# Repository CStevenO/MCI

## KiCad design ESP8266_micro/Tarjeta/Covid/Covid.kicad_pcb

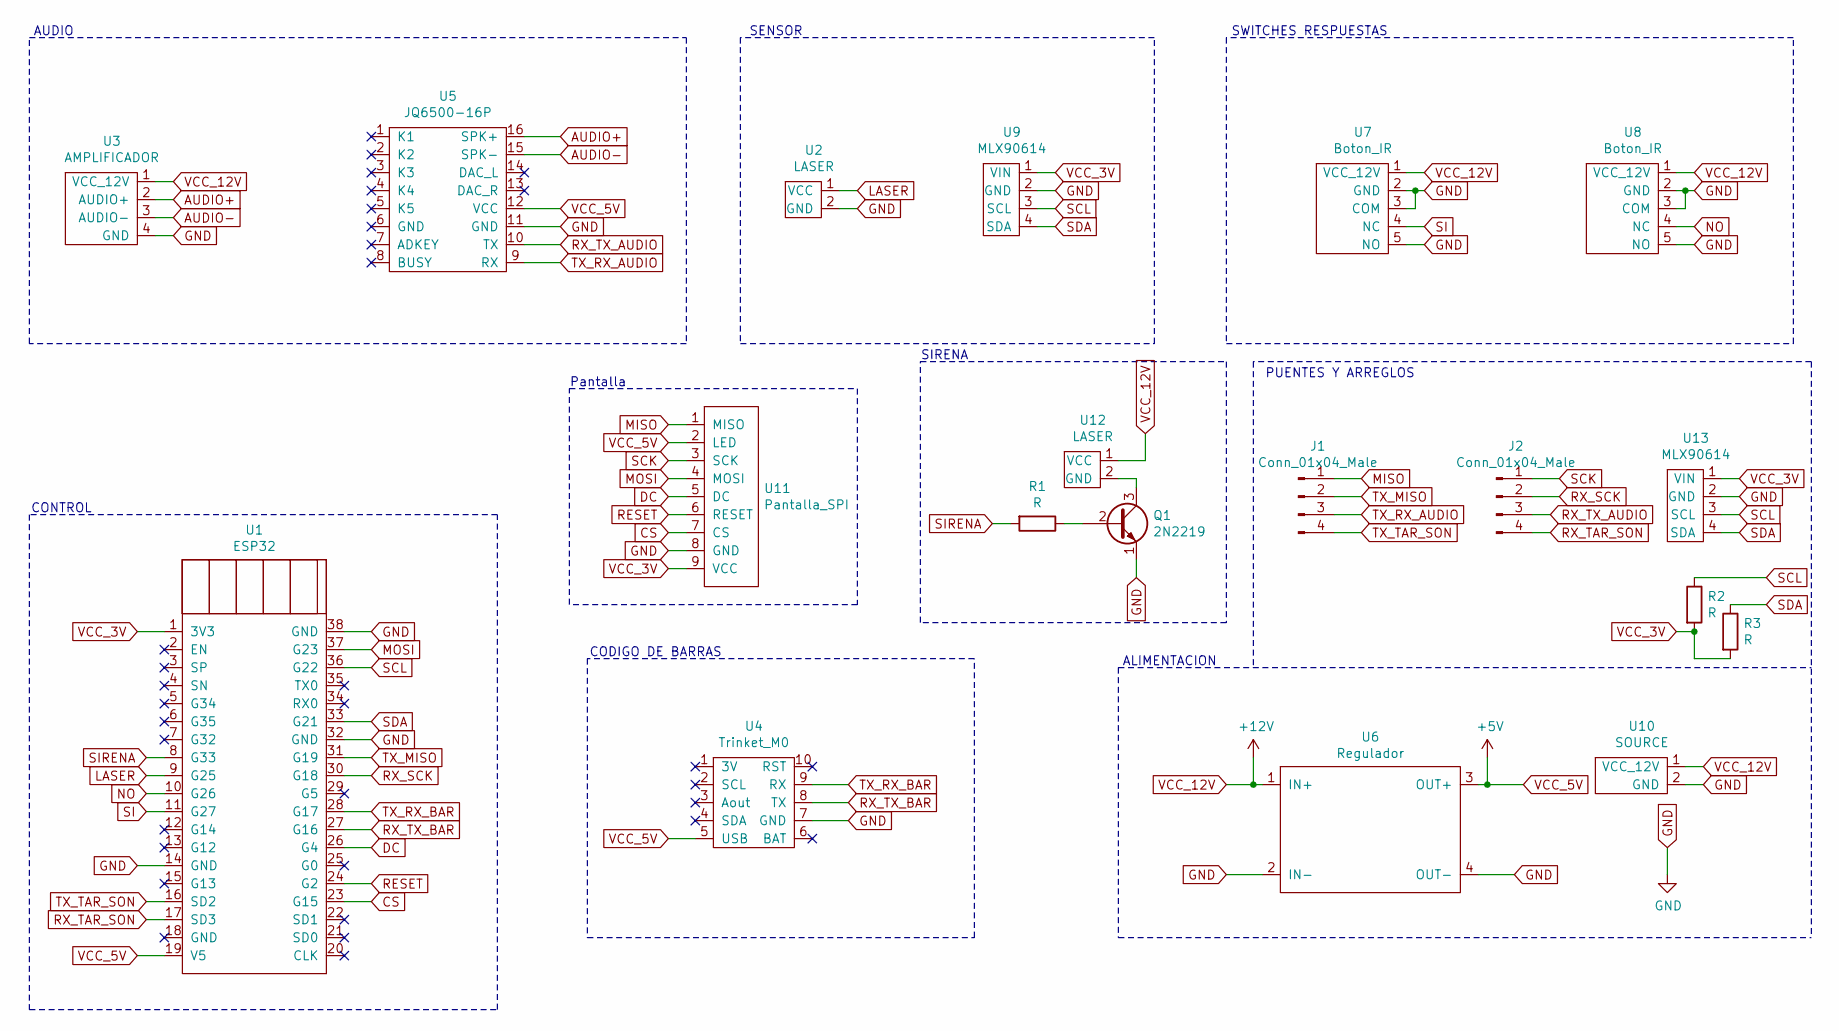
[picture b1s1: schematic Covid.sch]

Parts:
J1, J2: Conn_01x04_Male; TerminalBlock_TE_282834-4_1x04_P2.54mm_Horizontal
Q1: 2N2219; TO-92L_Inline
R1, R2, R3: R; R_Axial_DIN0309_L9.0mm_D3.2mm_P2.54mm_Vertical
U1: ESP32
U2, U12: LASER
U3: AMPLIFICADOR
U4: Trinket_M0; TRINKET_M0
U5: JQ6500-16P; JQ6500-16p
U6: Regulador
U7, U8: Boton_IR; BOTON_IR
U9: MLX90614; MXL90614
U10: SOURCE
U11: Pantalla_SPI; Pantalla_spi
U13: MLX90614; TerminalBlock_TE_282834-4_1x04_P2.54mm_Horizontal

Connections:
AUDIO+: U3.2 (AUDIO+), U5.16 (SPK+)
AUDIO-: U3.3 (AUDIO-), U5.15 (SPK-)
CS: U1.23 (G15), U11.7 (CS)
DC: U1.26 (G4), U11.5 (DC)
GND: Q1.1 (E), U1.14 (GND), U1.32 (GND), U1.38 (GND), U2.2 (GND), U3.4 (GND), U4.7 (GND), U5.11 (GND), U6.2 (IN-), U6.4 (OUT-), U7.2 (GND), U7.3 (COM), U7.5 (NO), U8.2 (GND), U8.3 (COM), U8.5 (NO), U9.2 (GND), U10.2 (GND), U11.8 (GND), U13.2 (GND)
LASER: U1.9 (G25), U2.1 (VCC)
MISO: J1.1, U11.1 (MISO)
MOSI: U1.37 (G23), U11.4 (MOSI)
NO: U1.10 (G26), U8.4 (NC)
unnamed: Q1.2 (B), R1.1
unnamed: Q1.3 (C), U12.2 (GND)
RESET: U1.24 (G2), U11.6 (RESET)
RX_SCK: J2.2, U1.30 (G18)
RX_TAR_SON: J2.4, U1.17 (SD3)
RX_TX_AUDIO: J2.3, U5.10 (TX)
RX_TX_BAR: U1.27 (G16), U4.8 (TX)
SCK: J2.1, U11.3 (SCK)
SCL: R2.1, U1.36 (G22), U9.3 (SCL), U13.3 (SCL)
SDA: R3.1, U1.33 (G21), U9.4 (SDA), U13.4 (SDA)
SI: U1.11 (G27), U7.4 (NC)
SIRENA: R1.2, U1.8 (G33)
TX_MISO: J1.2, U1.31 (G19)
TX_RX_AUDIO: J1.3, U5.9 (RX)
TX_RX_BAR: U1.28 (G17), U4.9 (RX)
TX_TAR_SON: J1.4, U1.16 (SD2)
VCC_3V: R2.2, R3.2, U1.1 (3V3), U9.1 (VIN), U11.9 (VCC), U13.1 (VIN)
VCC_5V: U1.19 (V5), U4.5 (USB), U5.12 (VCC), U6.3 (OUT+), U11.2 (LED)
VCC_12V: U3.1 (VCC_12V), U6.1 (IN+), U7.1 (VCC_12V), U8.1 (VCC_12V), U10.1 (VCC_12V), U12.1 (VCC)

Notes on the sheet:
CONTROL
CODIGO DE BARRAS
ALIMENTACION
AUDIO
SENSOR
SWITCHES RESPUESTAS
Pantalla
SIRENA
PUENTES Y ARREGLOS

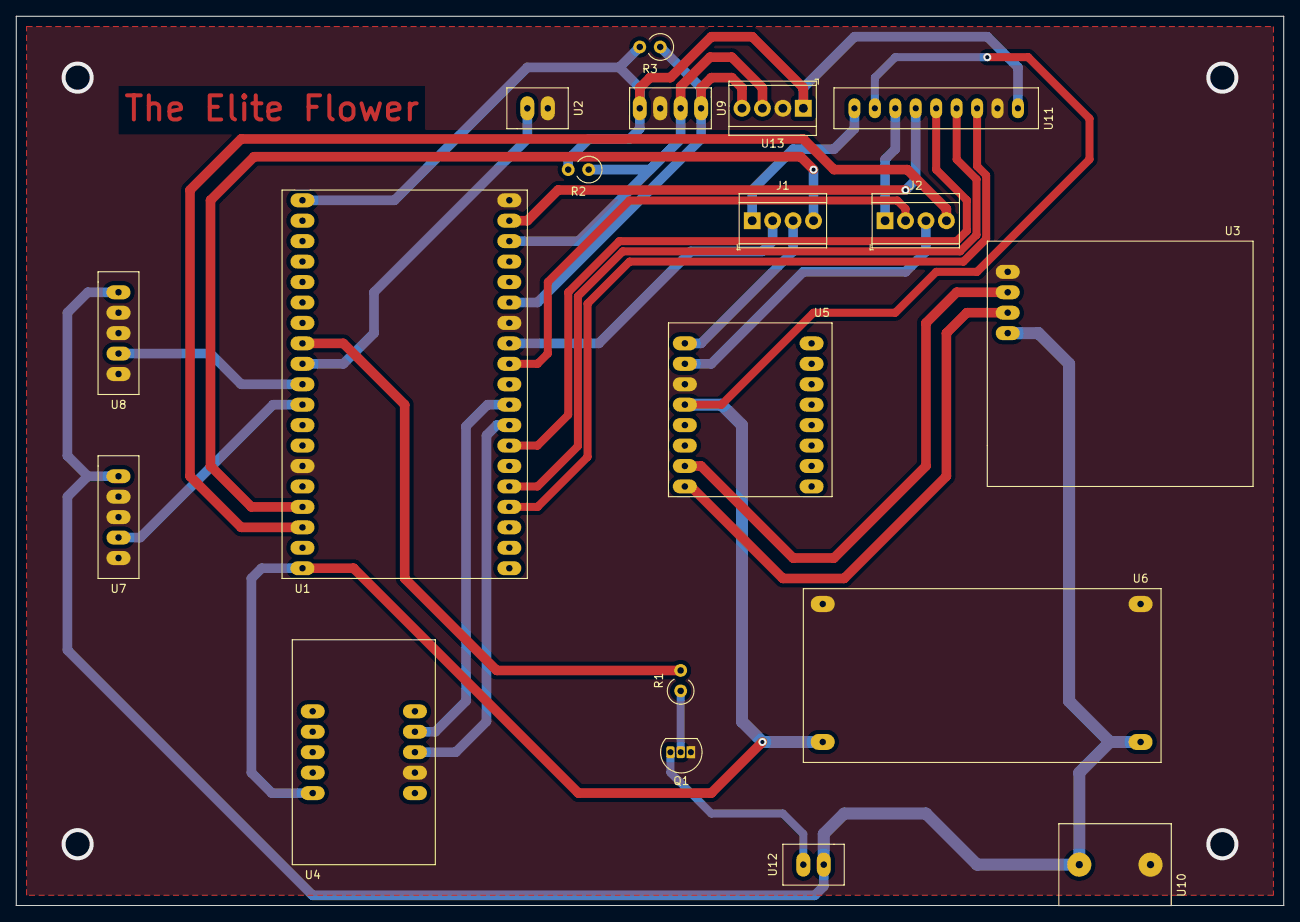
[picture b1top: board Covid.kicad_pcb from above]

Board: 2 copper layers, 157.5 x 110.5 mm, 19 parts (0 on the bottom side), 28 nets.

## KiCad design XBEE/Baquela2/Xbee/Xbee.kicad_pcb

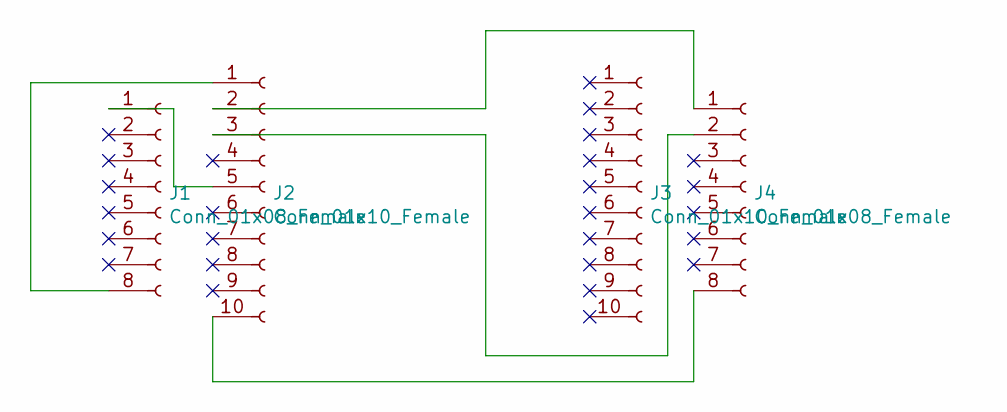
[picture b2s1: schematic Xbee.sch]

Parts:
J1, J4: Conn_01x08_Female; PinSocket_1x08_P2.54mm_Vertical
J2, J3: Conn_01x10_Female; PinSocket_1x10_P2.00mm_Vertical

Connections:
GND: J2.10, J4.8
unnamed: J1.1, J2.5
unnamed: J1.8, J2.1
unnamed: J2.2, J4.1
unnamed: J2.3, J4.2

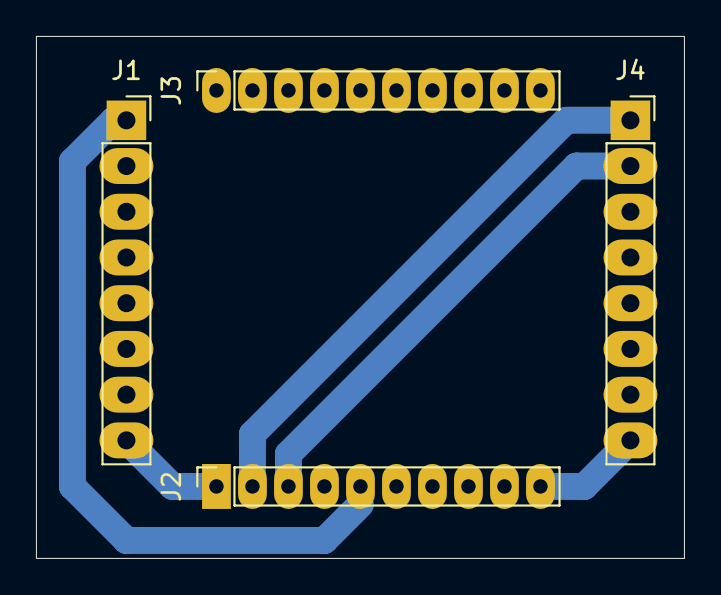
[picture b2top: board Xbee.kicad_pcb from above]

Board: 2 copper layers, 36.0 x 29.0 mm, 4 parts (0 on the bottom side), 5 nets.

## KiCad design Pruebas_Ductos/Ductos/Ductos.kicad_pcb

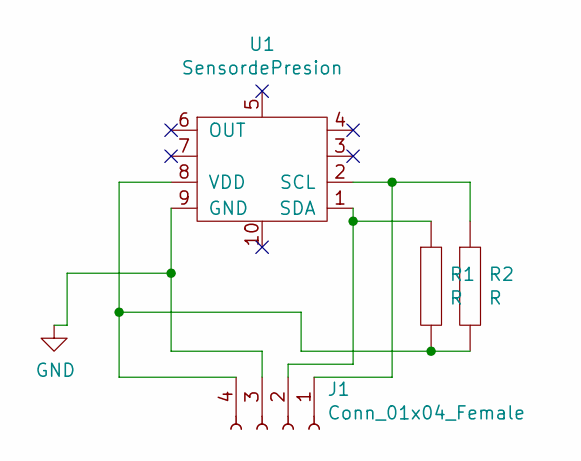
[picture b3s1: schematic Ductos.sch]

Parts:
J1: Conn_01x04_Female; TerminalBlock_Altech_AK300-4_P5.00mm
R1, R2: R; R_Axial_DIN0207_L6.3mm_D2.5mm_P10.16mm_Horizontal
U1: SensordePresion; SensorPresion

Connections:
GND: J1.3, U1.9 (GND)
unnamed: J1.1, R2.1, U1.2 (SCL)
unnamed: J1.2, R1.1, U1.1 (SDA)
unnamed: J1.4, R1.2, R2.2, U1.8 (VDD)

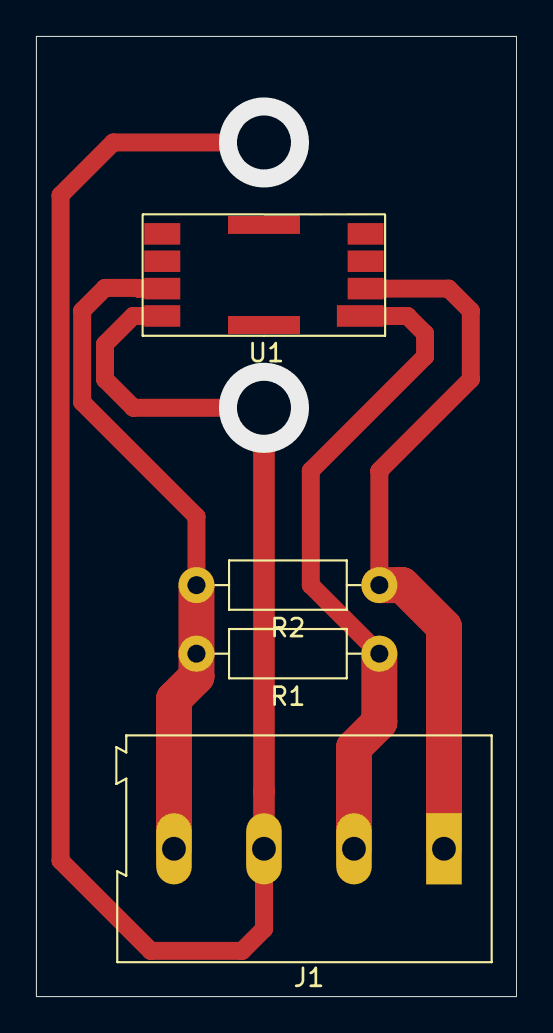
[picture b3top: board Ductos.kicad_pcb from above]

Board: 2 copper layers, 26.7 x 53.3 mm, 4 parts (0 on the bottom side), 4 nets.

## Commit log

2020-01-13 Text
    asd
2020-01-13 Create 1
2020-01-13 Archivos Subidos
2020-01-13 Archivos Para descomprimir
2020-01-14 Prueba colocando un espacio, sin cambiar nada del codigo.
2020-01-14 Se puede programar desde arduino y se envia a Github donde lo puedo guardar realmente o crearlo como un branch
2020-01-14 nada
2020-01-18 Descompresion
2020-01-21 pruebas con el sensor de humedad separado y sensor de temperatura
2020-01-23 Circuitos Ductos
2020-02-05 Avances en la libreria XBEE
2020-02-05 SE COMENTO EL RECEIVEPACKET
2020-02-05 no se que hice
2020-02-05 Arreglos
2020-02-08 Hola
2020-02-08 Ya compila, pero toca verificar por que no funciona
2020-02-11 Arreglos para que funcione
2020-02-15 arreglando la recepcion de informacion...
2020-02-18 ya recibe datos pero sí se cambia de tamaño el mensaje se bloquea :(
2020-02-19 Ya funciona la recepcion de informacion (pero la memoria dinamica no se esta borrando correctamente, así que quedo deshabilitada) y el estado de envio, falta revisar la tranmision de informacion
2020-02-21 ¿Ya se podrán enviar datos? (Falta prueba)
2020-02-21 tratando de arreglar pero no funciono
2020-02-27 XBEE libreria y pruebas varias, pero faltan más
2020-02-28 prueba para ductos (sensor de presion)
2020-03-10 eespac i i o
2020-03-10 dffyfyt
2020-03-10 cambios
2020-03-18 prueba
2020-03-19 ductos
2020-03-19 Muestra por serial
2020-03-25 Sublimacion
2020-03-25 varias sublimaciones al día
2020-03-25 programa de sublimacion para los invernaderos con XBEE
2020-04-29 no sé
2020-05-13 xbee
2020-05-13 Baquela XBEE
2020-06-02 no se
2020-06-17 toca probarlo
2020-06-17 niksd
2020-06-19 funcionalidades no probadas porque no tengo conexion con la red
2020-06-20 hora
2020-06-20 hlsvdjka
2020-06-22 asdfa
2020-06-23 Avances Covid
2020-06-23 esp32 funciona
2020-06-25 sensor de temperatura IR
2020-06-26 covid
2020-06-27 tarjeta
2020-06-27 datos de fabricacion
2020-06-30 funciona el barcode :D
2020-07-01 gerbers
2020-07-01 pruebas
2020-07-06 PCB con Pantalla SPI
2020-07-06 arreglos en el codigo
2020-07-07 baquelas
2020-07-08 quien sabe
2020-07-09 yhghjg
2020-07-10 mjyg,jgj
2020-07-11 jyjhgj
2020-07-11 ZDASD
2020-07-11 jfjhfhj
2020-07-13 jbasda
2020-07-16 zxccz
2020-07-16 fsdasda
2020-07-16 sfdfdb
2020-07-21 erqweqw
2020-07-21 sadasda
2020-07-22 sadasd
2020-07-22 asdasda
2020-07-22 jasdbasbdjab
2020-08-04 arreglos?
2020-08-27 mejoras totales
    no me acuerdo cuales fueron los arreglos que hice
2020-09-02 arreglos en invernaderos
2020-09-03 Avances sustanciales, falta arreglar el codigo deñ arduino para que reciba datos de configuracion,hora, y pueda enviar datos
2020-09-07 arreglos varios
2020-09-08 arreglos en los horarios para activarse por horarios programados
2020-09-09 No me acuerdo que fue lo que hice
2020-09-14 asdas
2020-09-14 jgcjgvg
2020-09-15 arreglos faltan pruebas de control de dispostivos
2020-09-18 arreglos generales
2020-09-23 arreglos varios
    arreglos variados
2020-09-30 Flujo
    Flujo de Node-red
